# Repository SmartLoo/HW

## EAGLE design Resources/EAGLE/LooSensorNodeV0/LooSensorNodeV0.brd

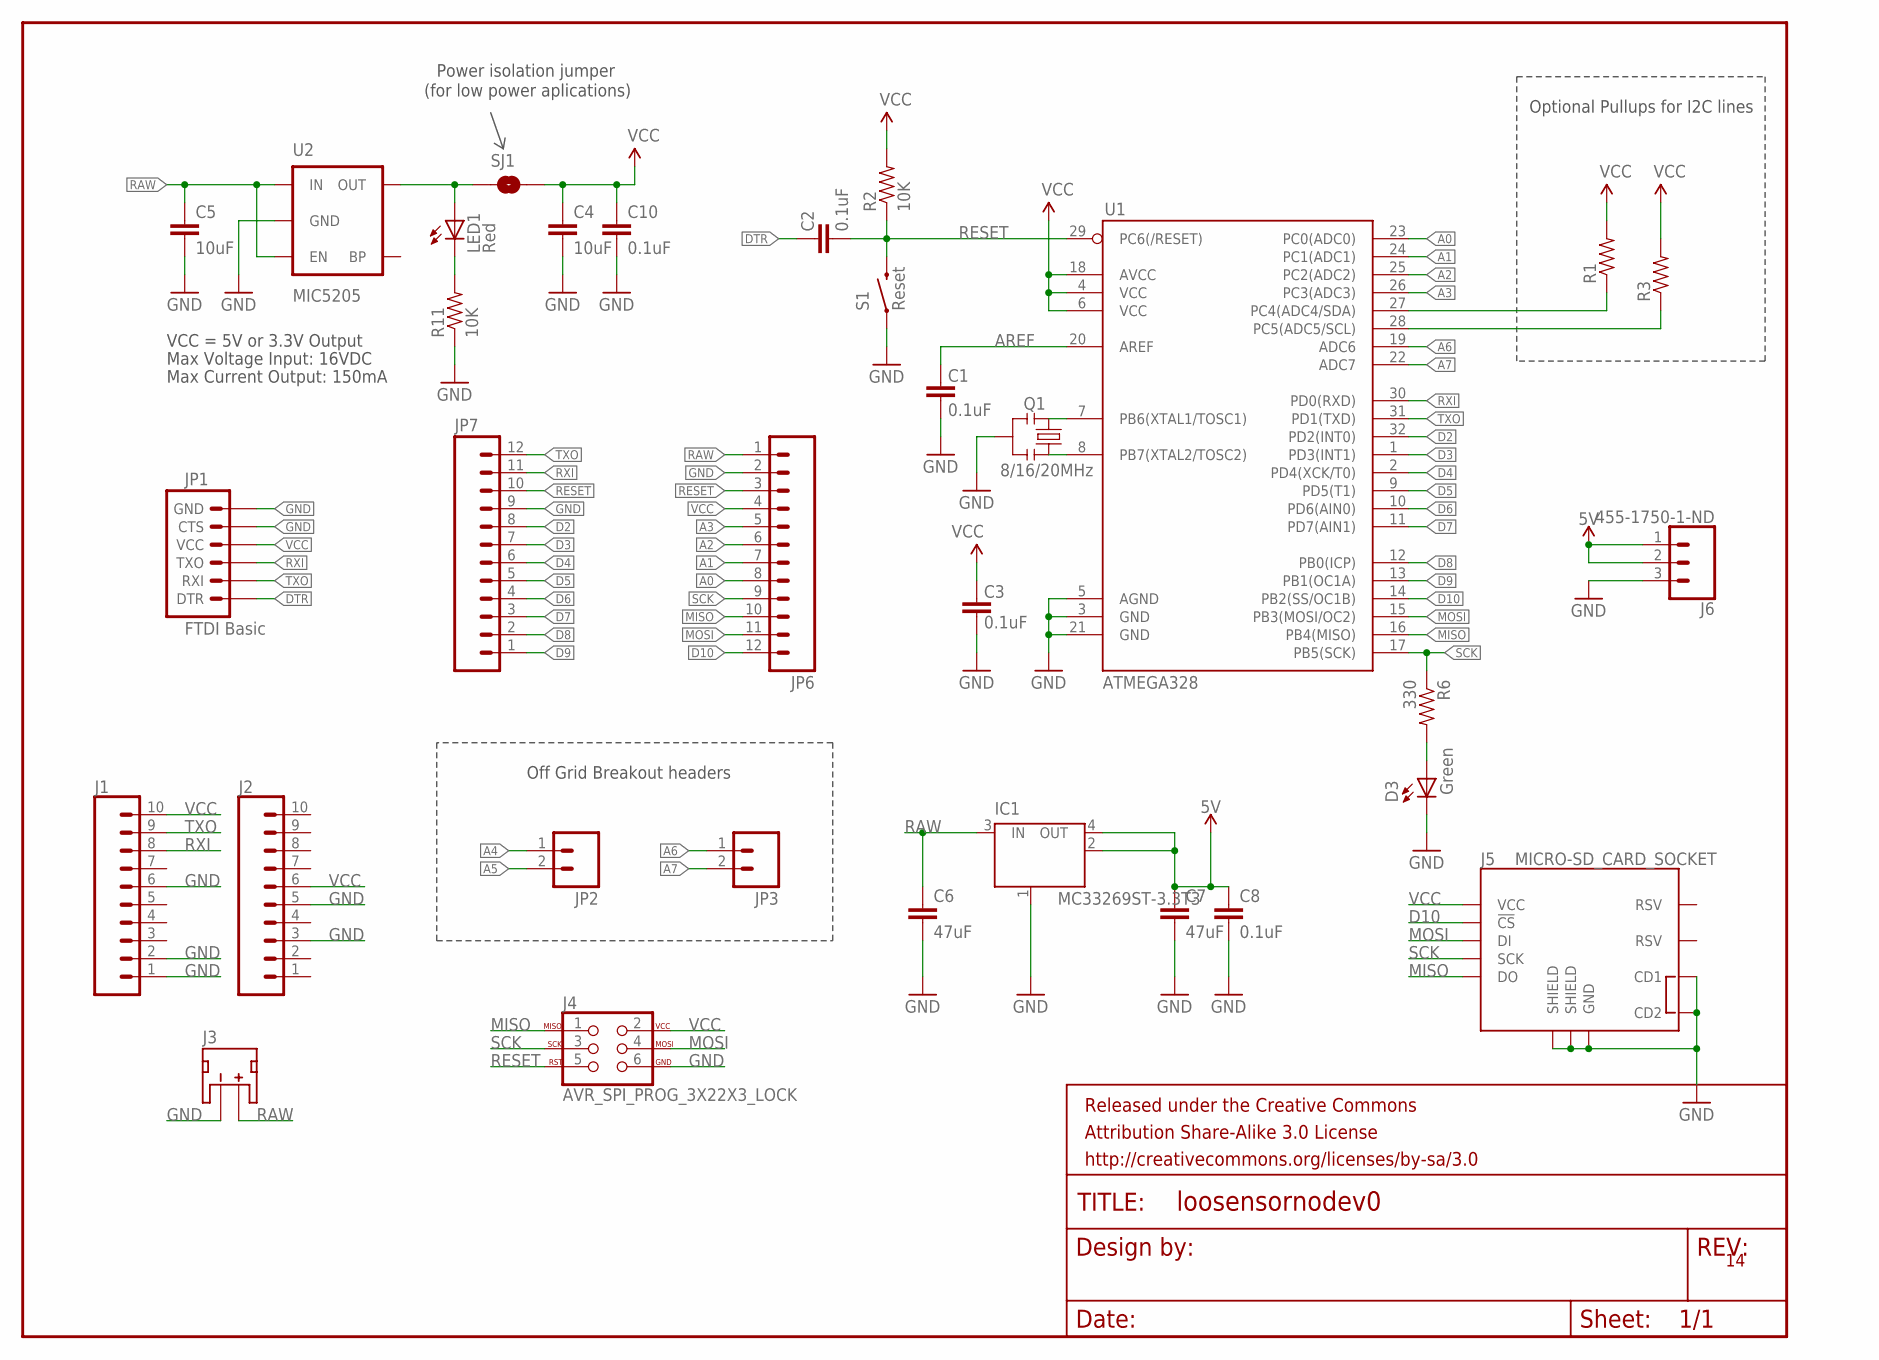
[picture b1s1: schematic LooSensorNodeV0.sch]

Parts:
C1, C2, C3, C10: 0.1uF; 0603-CAP
C4, C5: 10uF; 0603
C6, C7: 47uF; 1210
C8: 0.1uF; 0603
D3: Green; 0603-LED-ALT1
FRAME1: FRAME-LETTER; CREATIVE_COMMONS
IC1: MC33269ST-3.3T3; SOT223
J1, J2: CONN_102MM; 1X10-2MM
J3: JST_2MM_MALE; JST-2-SMD
J4: AVR_SPI_PROG_3X22X3_LOCK; 2X3_LOCK
J5: MICRO-SD_CARD_SOCKET; MICRO-SD-SOCKET
J6: 455-1750-1-ND; 1X03
JP1: FTDI Basic; 1X06
JP2, JP3: M02PTH; 1X02
JP6, JP7: M12PTH; 1X12
LED1: Red; 0603-LED-ALT1
Q1: 8/16/20MHz; RESONATOR-SMD-1:1
R1, R3: RESISTOR0603-RES; 0603-RES
R2, R11: 10K; 0603-RES
R6: 330; 0603-RES
S1: Reset; TACTILE-SWITCH-SMD-ALT01
SJ1: SOLDERJUMPERNC; SJ_2S
U1: ATMEGA328; TQFP32-08
U2: MIC5205; SOT23-5

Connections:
5V: C7.1, C8.1, IC1.2 (OUT), IC1.4 (OUT), J6.1, J6.2
A0: JP6.8, U1.23 (PC0(ADC0))
A1: JP6.7, U1.24 (PC1(ADC1))
A2: JP6.6, U1.25 (PC2(ADC2))
A3: JP6.5, U1.26 (PC3(ADC3))
A4: JP2.1, R1.1, U1.27 (PC4(ADC4/SDA))
A5: JP2.2, R3.1, U1.28 (PC5(ADC5/SCL))
A6: JP3.1, U1.19 (ADC6)
A7: JP3.2, U1.22 (ADC7)
AREF: C1.2, U1.20 (AREF)
D2: JP7.8, U1.32 (PD2(INT0))
D3: JP7.7, U1.1 (PD3(INT1))
D4: JP7.6, U1.2 (PD4(XCK/T0))
D5: JP7.5, U1.9 (PD5(T1))
D6: JP7.4, U1.10 (PD6(AIN0))
D7: JP7.3, U1.11 (PD7(AIN1))
D8: JP7.2, U1.12 (PB0(ICP))
D9: JP7.1, U1.13 (PB1(OC1A))
D10: J5.CS (!CS), JP6.12, U1.14 (PB2(SS/OC1B))
DTR: C2.2, JP1.1 (DTR)
GND: C1.1, C3.1, C4.2, C5.2, C6.2, C7.2, C8.2, C10.2, D3.C, IC1.1 (GND/ADJ), J1.1, J1.2, J1.6, J2.3, J2.5, J3.1 (-), J4.6, J5.CD1, J5.CD2, J5.GND, J5.GND1 (SHIELD), J5.GND3 (SHIELD), J6.3, JP1.5 (CTS), JP1.6 (GND), JP6.2, JP7.9, Q1.2, R11.1, S1.1, S1.2 (1), U1.3 (GND), U1.5 (AGND), U1.21 (GND), U2.2 (GND)
MISO: J4.1, J5.DO, JP6.10, U1.16 (PB4(MISO))
MOSI: J4.4, J5.DI, JP6.11, U1.15 (PB3(MOSI/OC2))
unnamed: Q1.3, U1.8 (PB7(XTAL2/TOSC2))
unnamed: Q1.1, U1.7 (PB6(XTAL1/TOSC1))
unnamed: LED1.A, SJ1.1, U2.5 (OUT)
unnamed: LED1.C, R11.2
unnamed: D3.A, R6.2
RAW: C5.1, C6.1, IC1.3 (IN), J3.2 (+), JP6.1, U2.1 (IN), U2.3 (EN)
RESET: C2.1, J4.5, JP6.3, JP7.10, R2.1, S1.3 (2), S1.4 (2), U1.29 (PC6(/RESET))
RXI: J1.8, JP1.3 (TXO), JP7.11, U1.30 (PD0(RXD))
SCK: J4.3, J5.SCLK (SCK), JP6.9, R6.1, U1.17 (PB5(SCK))
TXO: J1.9, JP1.2 (RXI), JP7.12, U1.31 (PD1(TXD))
VCC: C3.2, C4.1, C10.1, J1.10, J2.6, J4.2, J5.VCC, JP1.4 (VCC), JP6.4, R1.2, R2.2, R3.2, SJ1.2, U1.4 (VCC), U1.6 (VCC), U1.18 (AVCC)

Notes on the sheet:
Max Voltage Input: 16VDC
Max Current Output: 150mA
VCC = 5V or 3.3V Output
Optional Pullups for I2C lines
Off Grid Breakout headers
Power isolation jumper
(for low power aplications)

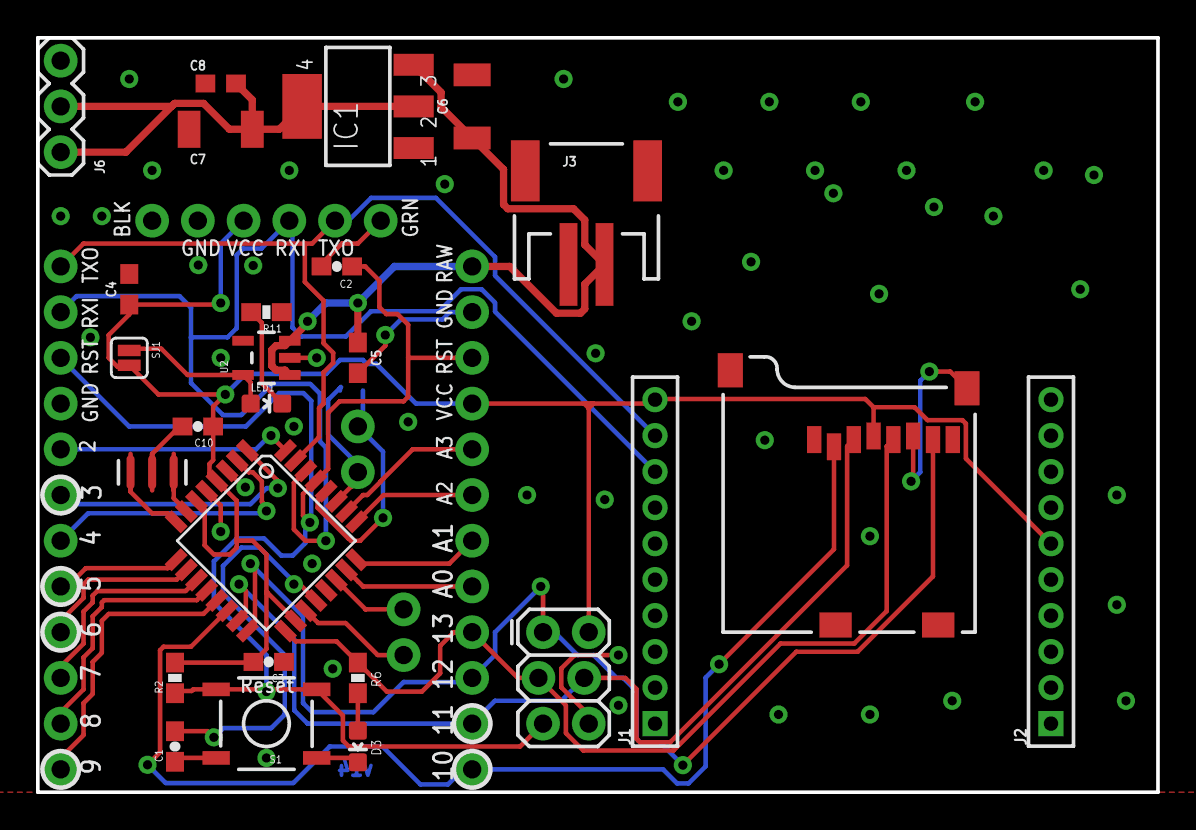
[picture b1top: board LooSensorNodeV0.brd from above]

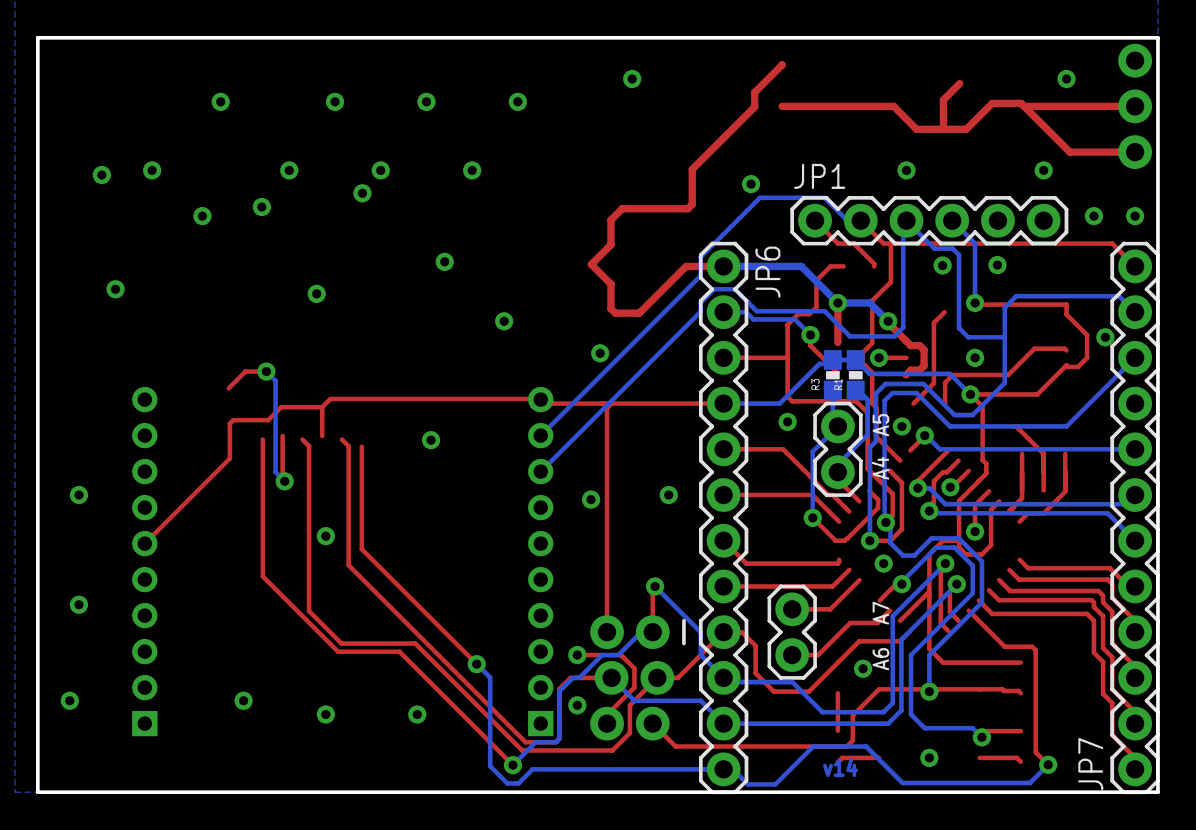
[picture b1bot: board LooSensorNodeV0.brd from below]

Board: 2 copper layers, 62.2 x 41.9 mm, 34 parts (7 on the bottom side), 34 nets.

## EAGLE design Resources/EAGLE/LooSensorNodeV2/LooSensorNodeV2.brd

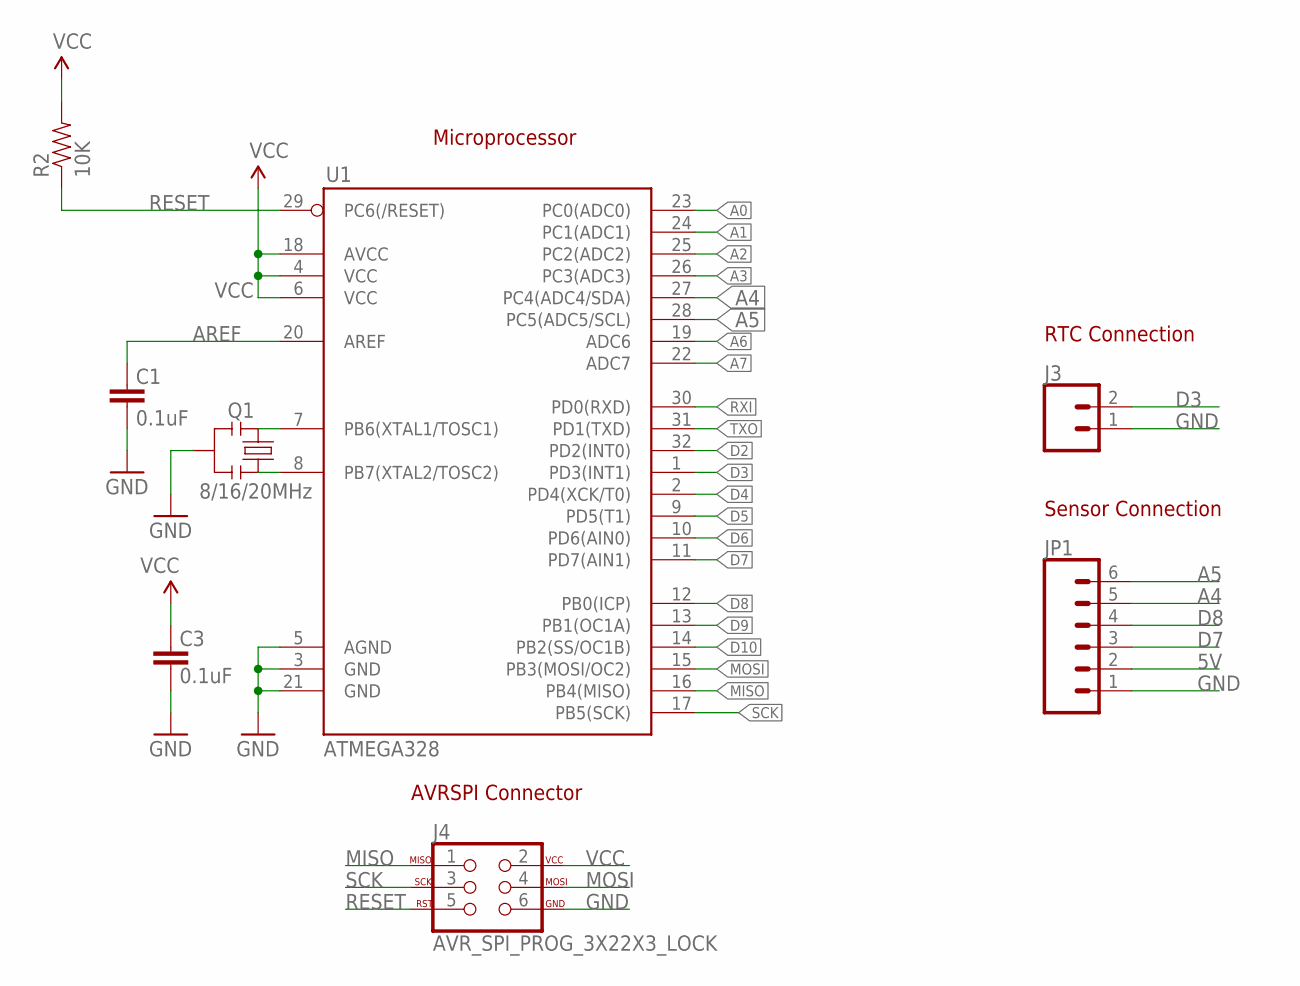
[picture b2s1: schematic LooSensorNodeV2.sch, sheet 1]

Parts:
C1, C3: 0.1uF; 0603-CAP
J3: CONN_02; 1X02
J4: AVR_SPI_PROG_3X22X3_LOCK; 2X3_LOCK
JP1: CONN_06SILK_FEMALE_PTH; 1X06
Q1: 8/16/20MHz; RESONATOR-SMD-1:1
R2: 10K; 0603-RES
U1: ATMEGA328; TQFP32-08

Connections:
5V: JP1.2; also elsewhere on the board
A0: U1.23 (PC0(ADC0))
A1: U1.24 (PC1(ADC1))
A2: U1.25 (PC2(ADC2))
A3: U1.26 (PC3(ADC3))
A4: JP1.5, U1.27 (PC4(ADC4/SDA))
A5: JP1.6, U1.28 (PC5(ADC5/SCL))
A6: U1.19 (ADC6)
A7: U1.22 (ADC7)
AREF: C1.2, U1.20 (AREF)
D2: U1.32 (PD2(INT0))
D3: J3.2, U1.1 (PD3(INT1))
D4: U1.2 (PD4(XCK/T0)); also elsewhere on the board
D5: U1.9 (PD5(T1))
D6: U1.10 (PD6(AIN0)); also elsewhere on the board
D7: JP1.3, U1.11 (PD7(AIN1))
D8: JP1.4, U1.12 (PB0(ICP))
D9: U1.13 (PB1(OC1A))
D10: U1.14 (PB2(SS/OC1B))
GND: C1.1, C3.1, J3.1, J4.6, JP1.1, Q1.2, U1.3 (GND), U1.5 (AGND), U1.21 (GND); also elsewhere on the board
MISO: J4.1, U1.16 (PB4(MISO))
MOSI: J4.4, U1.15 (PB3(MOSI/OC2))
unnamed: Q1.3, U1.8 (PB7(XTAL2/TOSC2))
unnamed: Q1.1, U1.7 (PB6(XTAL1/TOSC1))
RESET: J4.5, R2.1, U1.29 (PC6(/RESET))
RXI: U1.30 (PD0(RXD)); also elsewhere on the board
SCK: J4.3, U1.17 (PB5(SCK))
TXO: U1.31 (PD1(TXD)); also elsewhere on the board
VCC: C3.2, J4.2, R2.2, U1.4 (VCC), U1.6 (VCC), U1.18 (AVCC); also elsewhere on the board

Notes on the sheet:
AVRSPI Connector
Microprocessor
Sensor Connection
RTC Connection

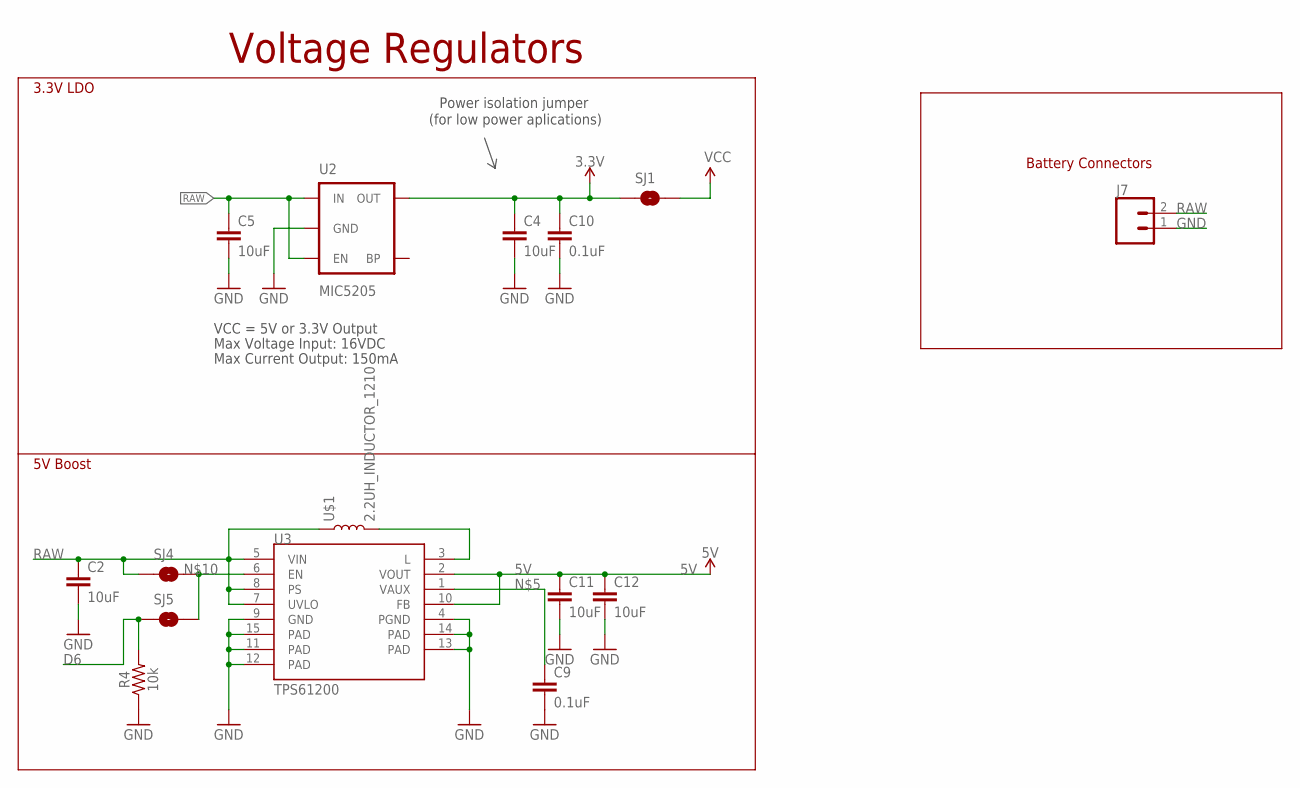
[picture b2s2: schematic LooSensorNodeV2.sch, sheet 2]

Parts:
C2, C4, C5, C11, C12: 10uF; 0603
C9: 0.1uF; 0603
C10: 0.1uF; 0603-CAP
J7: CONN_02; 1X02
R4: 10k; 0603
SJ1, SJ4, SJ5: SOLDERJUMPERNC; SJ_2S
U2: MIC5205; SOT23-5
U3: TPS61200; QFN-10_PAD
U$1: 2.2UH_INDUCTOR_1210; 1210

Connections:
3.3V: C4.1, C10.1, SJ1.1, U2.5 (OUT); also elsewhere on the board
5V: C11.1, C12.1, U3.2 (VOUT), U3.10 (FB); also elsewhere on the board
D6: R4.2, SJ5.1; also elsewhere on the board
GND: C2.2, C4.2, C5.2, C9.2, C10.2, C11.2, C12.2, J7.1, R4.1, U2.2 (GND), U3.4 (PGND), U3.9 (GND), U3.11 (PAD), U3.12 (PAD), U3.13 (PAD), U3.14 (PAD), U3.15 (PAD); also elsewhere on the board
unnamed: C9.1, U3.1 (VAUX)
unnamed: U3.3 (L), U$1.2
unnamed: SJ4.2, SJ5.2, U3.6 (EN)
RAW: C2.1, C5.1, J7.2, SJ4.1, U2.1 (IN), U2.3 (EN), U3.5 (VIN), U3.7 (UVLO), U3.8 (PS), U$1.1
VCC: SJ1.2; also elsewhere on the board

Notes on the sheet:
Max Voltage Input: 16VDC
Max Current Output: 150mA
VCC = 5V or 3.3V Output
Power isolation jumper
(for low power aplications)
3.3V LDO
5V Boost
Voltage Regulators
Battery Connectors

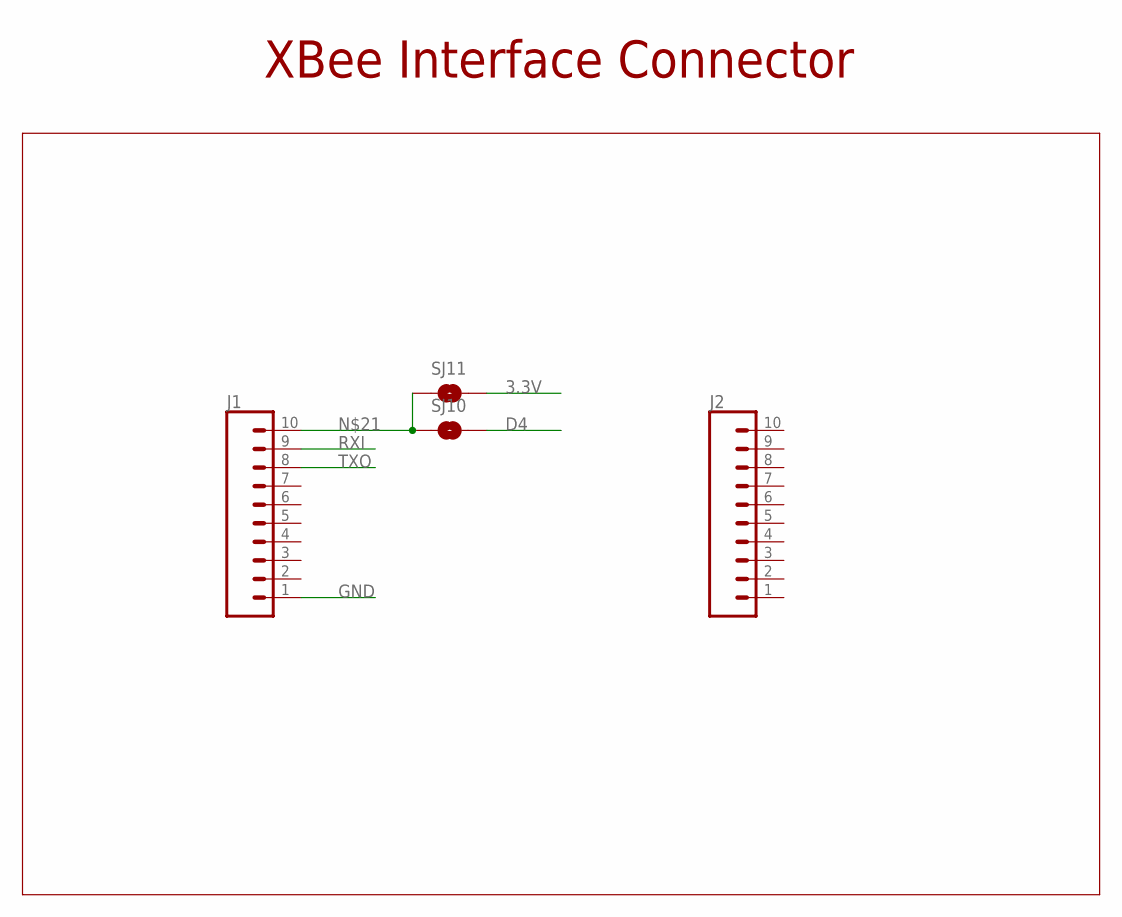
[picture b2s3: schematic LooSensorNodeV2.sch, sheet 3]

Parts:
J1, J2: CONN_102MM; 1X10-2MM
SJ10, SJ11: SOLDERJUMPERNC; SJ_2S

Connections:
3.3V: SJ11.2; also elsewhere on the board
D4: SJ10.2; also elsewhere on the board
GND: J1.1; also elsewhere on the board
unnamed: J1.10, SJ10.1, SJ11.1
RXI: J1.9; also elsewhere on the board
TXO: J1.8; also elsewhere on the board

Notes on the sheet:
XBee Interface Connector

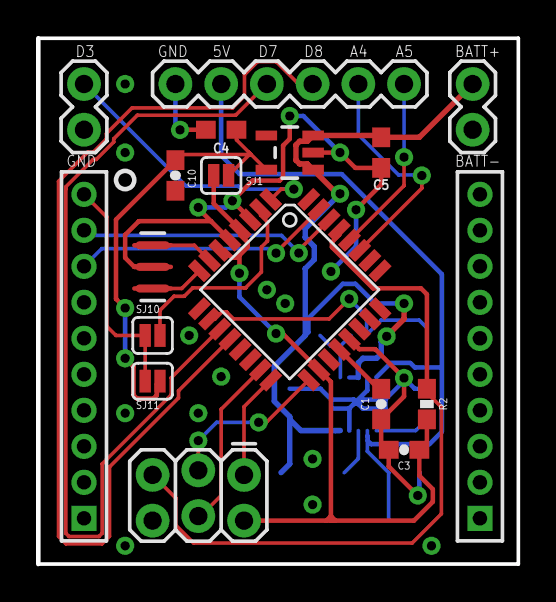
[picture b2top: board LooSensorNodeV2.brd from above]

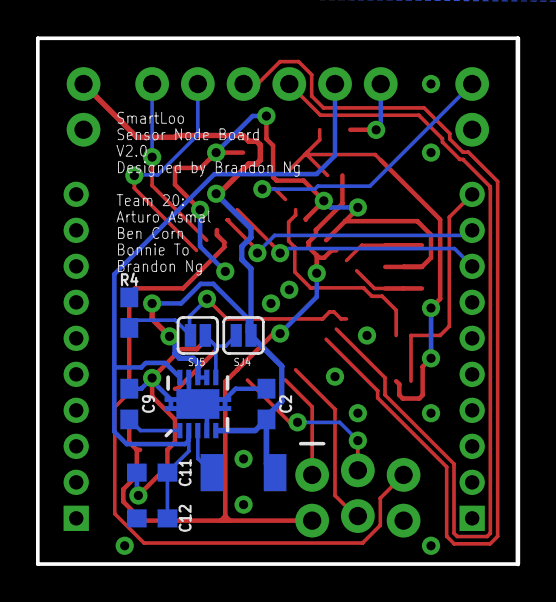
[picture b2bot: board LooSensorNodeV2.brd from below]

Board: 2 copper layers, 26.6 x 29.2 mm, 27 parts (9 on the bottom side), 25 nets.

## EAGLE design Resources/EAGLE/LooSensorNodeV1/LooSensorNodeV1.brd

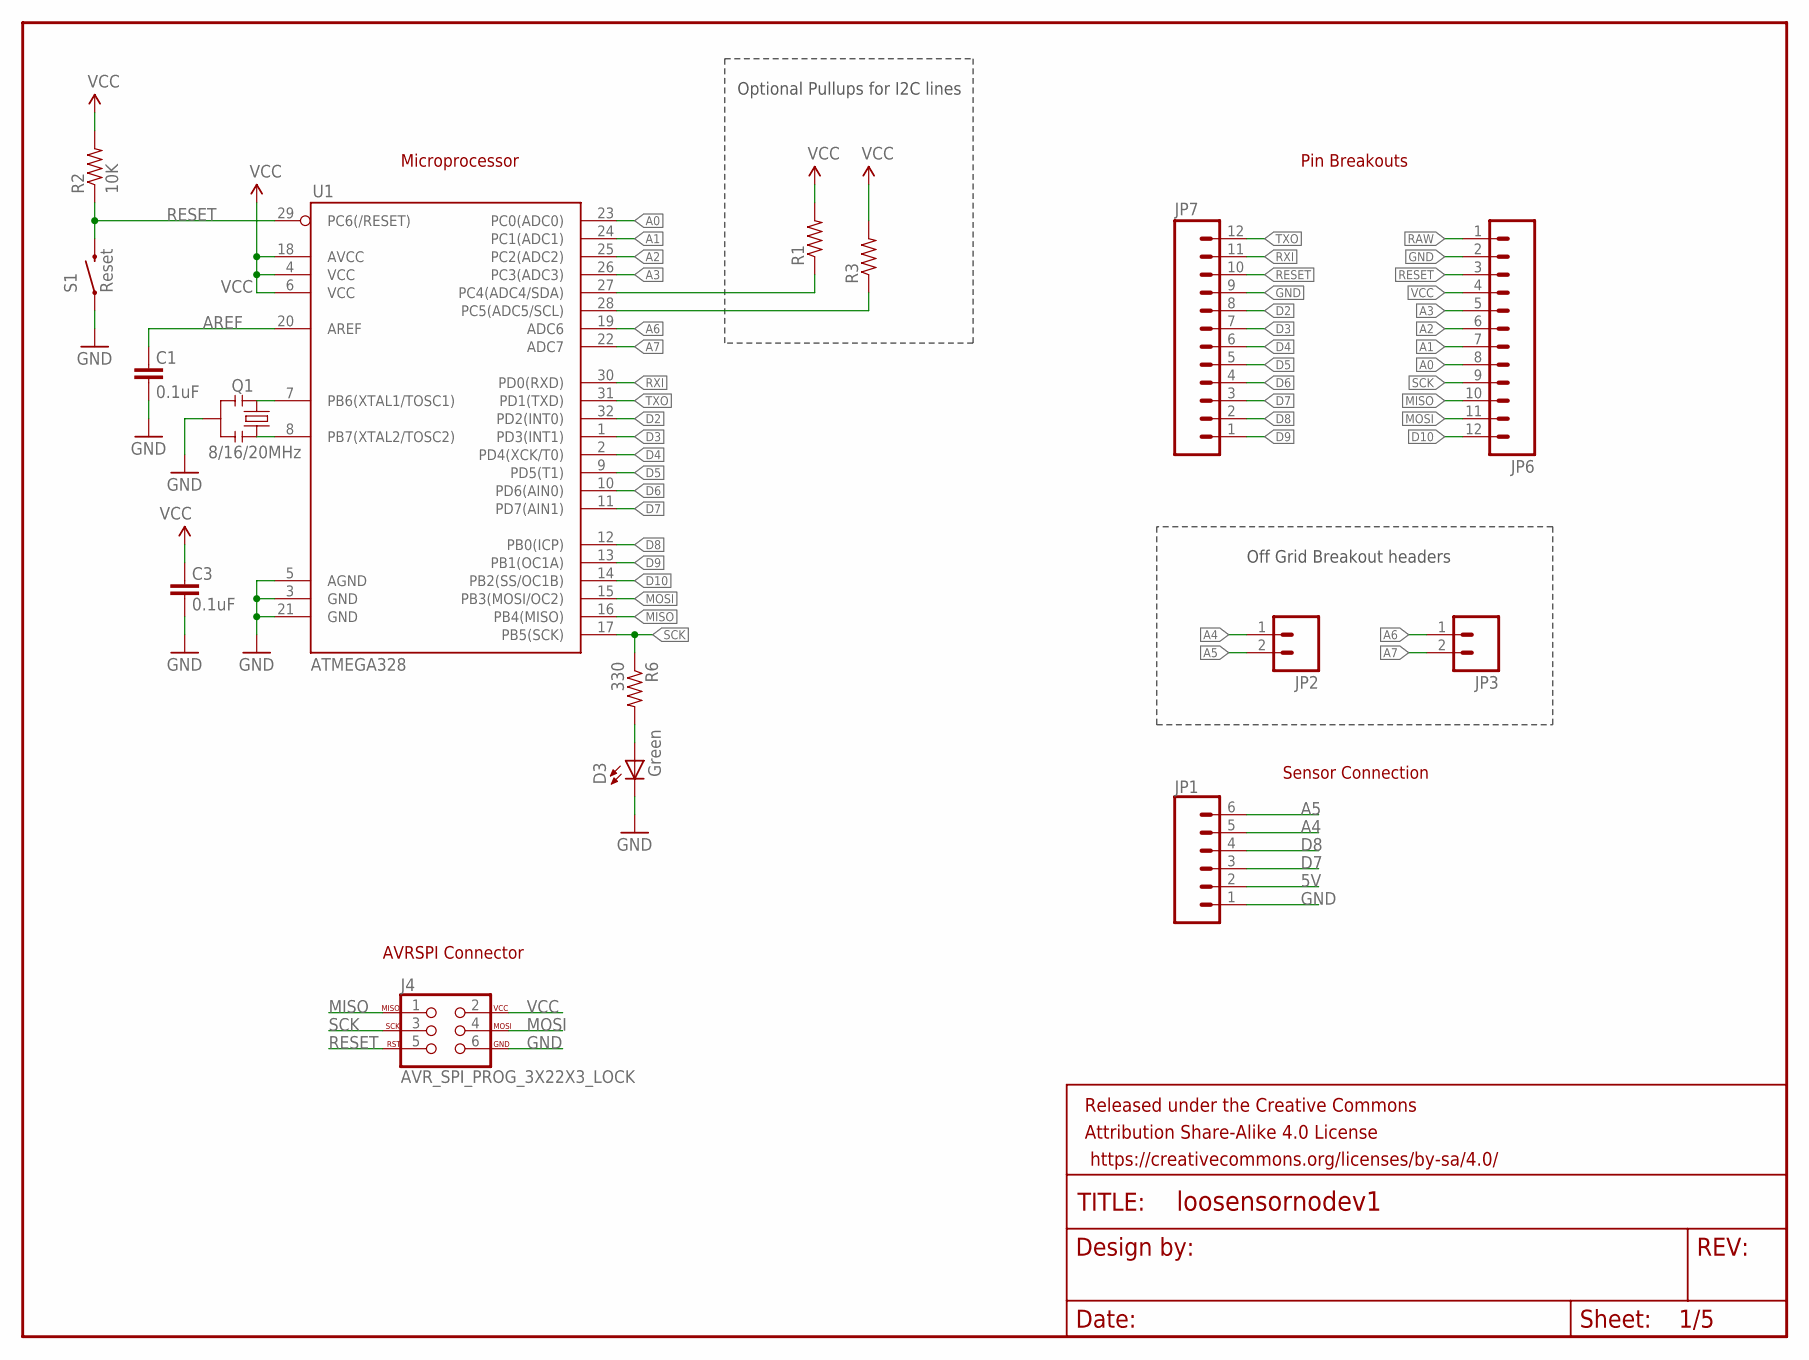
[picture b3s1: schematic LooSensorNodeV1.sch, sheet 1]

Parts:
C1, C3: 0.1uF; 0603-CAP
D3: Green; 0603-LED-ALT1
FRAME1: FRAME-LETTER; CREATIVE_COMMONS
J4: AVR_SPI_PROG_3X22X3_LOCK; 2X3_LOCK
JP1: CONN_06SILK_FEMALE_PTH; 1X06
JP2, JP3: M02PTH; 1X02
JP6, JP7: M12PTH; 1X12
Q1: 8/16/20MHz; RESONATOR-SMD-1:1
R1, R3: RESISTOR0603-RES; 0603-RES
R2: 10K; 0603-RES
R6: 330; 0603-RES
S1: Reset; TACTILE-SWITCH-SMD-ALT01
U1: ATMEGA328; TQFP32-08

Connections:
5V: JP1.2; also elsewhere on the board
A0: JP6.8, U1.23 (PC0(ADC0))
A1: JP6.7, U1.24 (PC1(ADC1))
A2: JP6.6, U1.25 (PC2(ADC2))
A3: JP6.5, U1.26 (PC3(ADC3))
A4: JP1.5, JP2.1, R1.1, U1.27 (PC4(ADC4/SDA)); also elsewhere on the board
A5: JP1.6, JP2.2, R3.1, U1.28 (PC5(ADC5/SCL)); also elsewhere on the board
A6: JP3.1, U1.19 (ADC6)
A7: JP3.2, U1.22 (ADC7)
AREF: C1.2, U1.20 (AREF)
D2: JP7.8, U1.32 (PD2(INT0)); also elsewhere on the board
D3: JP7.7, U1.1 (PD3(INT1))
D4: JP7.6, U1.2 (PD4(XCK/T0)); also elsewhere on the board
D5: JP7.5, U1.9 (PD5(T1)); also elsewhere on the board
D6: JP7.4, U1.10 (PD6(AIN0)); also elsewhere on the board
D7: JP1.3, JP7.3, U1.11 (PD7(AIN1))
D8: JP1.4, JP7.2, U1.12 (PB0(ICP))
D9: JP7.1, U1.13 (PB1(OC1A))
D10: JP6.12, U1.14 (PB2(SS/OC1B)); also elsewhere on the board
GND: C1.1, C3.1, D3.C, J4.6, JP1.1, JP6.2, JP7.9, Q1.2, S1.1, S1.2 (1), U1.3 (GND), U1.5 (AGND), U1.21 (GND); also elsewhere on the board
MISO: J4.1, JP6.10, U1.16 (PB4(MISO)); also elsewhere on the board
MOSI: J4.4, JP6.11, U1.15 (PB3(MOSI/OC2)); also elsewhere on the board
unnamed: Q1.3, U1.8 (PB7(XTAL2/TOSC2))
unnamed: Q1.1, U1.7 (PB6(XTAL1/TOSC1))
unnamed: D3.A, R6.2
RAW: JP6.1; also elsewhere on the board
RESET: J4.5, JP6.3, JP7.10, R2.1, S1.3 (2), S1.4 (2), U1.29 (PC6(/RESET))
RXI: JP7.11, U1.30 (PD0(RXD)); also elsewhere on the board
SCK: J4.3, JP6.9, R6.1, U1.17 (PB5(SCK)); also elsewhere on the board
TXO: JP7.12, U1.31 (PD1(TXD)); also elsewhere on the board
VCC: C3.2, J4.2, JP6.4, R1.2, R2.2, R3.2, U1.4 (VCC), U1.6 (VCC), U1.18 (AVCC); also elsewhere on the board

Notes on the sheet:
Optional Pullups for I2C lines
Off Grid Breakout headers
AVRSPI Connector
Pin Breakouts
Microprocessor
Sensor Connection

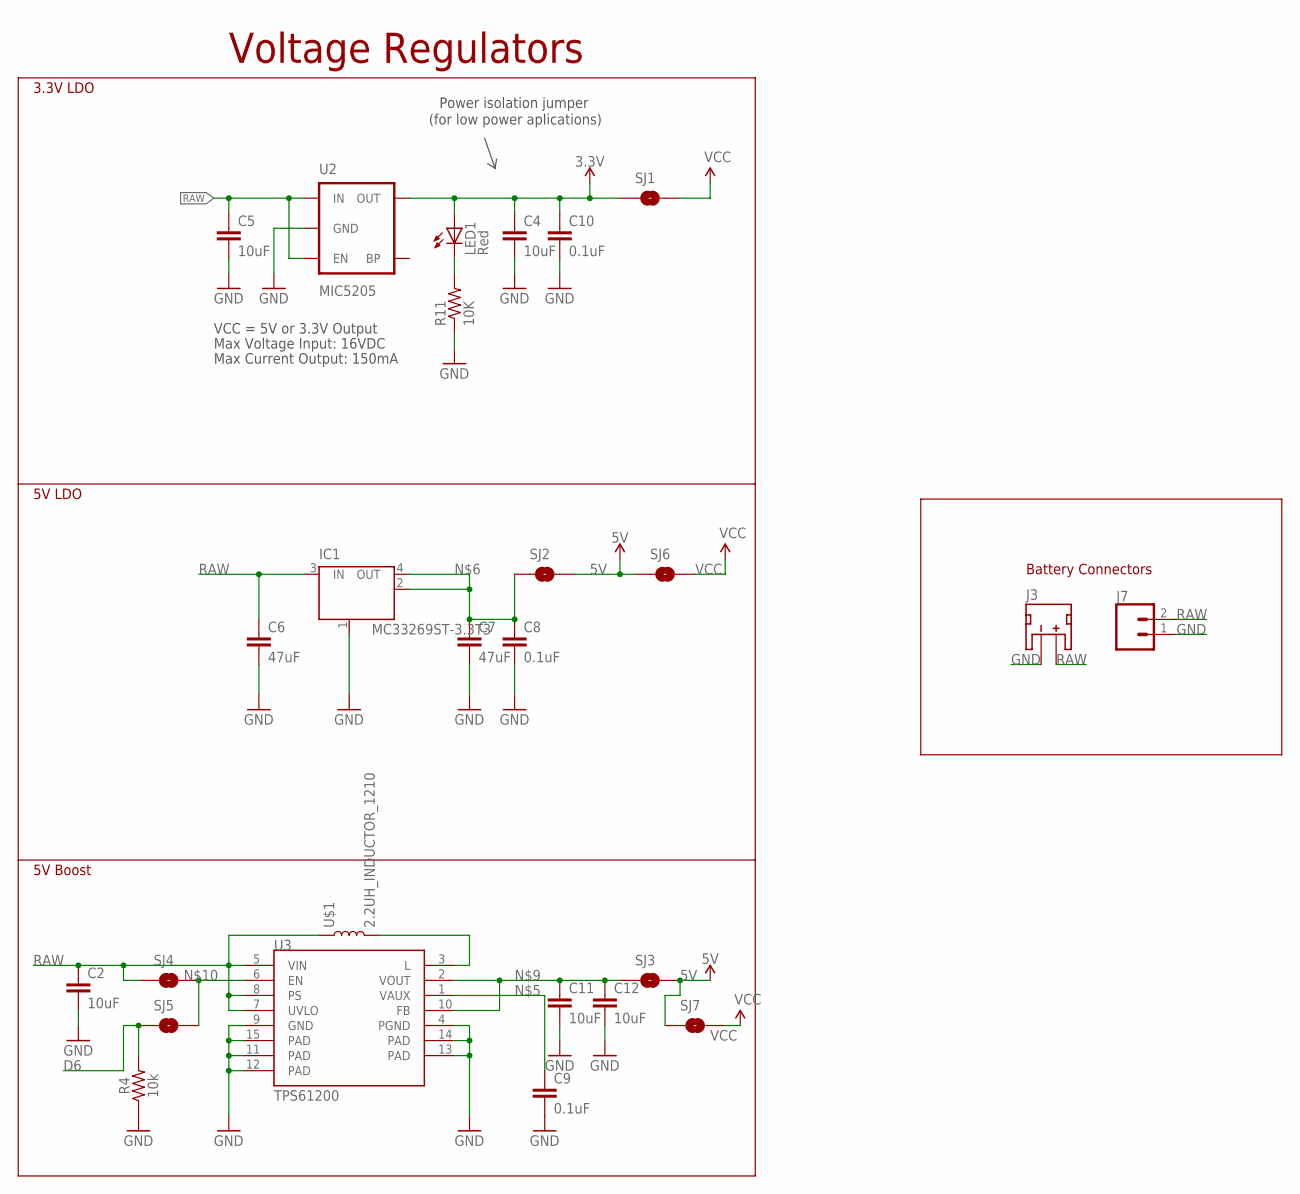
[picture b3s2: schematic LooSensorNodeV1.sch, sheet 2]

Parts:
C2, C4, C5, C11, C12: 10uF; 0603
C6, C7: 47uF; 1210
C8, C9: 0.1uF; 0603
C10: 0.1uF; 0603-CAP
IC1: MC33269ST-3.3T3; SOT223
J3: JST_2MM_MALE; JST-2-SMD
J7: CONN_02; 1X02
LED1: Red; 0603-LED-ALT1
R4: 10k; 0603
R11: 10K; 0603-RES
SJ1, SJ2, SJ3, SJ4, SJ5, SJ6, SJ7: SOLDERJUMPERNC; SJ_2S
U2: MIC5205; SOT23-5
U3: TPS61200; QFN-10_PAD
U$1: 2.2UH_INDUCTOR_1210; 1210

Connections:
3.3V: C4.1, C10.1, LED1.A, SJ1.1, U2.5 (OUT); also elsewhere on the board
5V: SJ2.2, SJ3.2, SJ6.1, SJ7.1; also elsewhere on the board
D6: R4.2, SJ5.1; also elsewhere on the board
GND: C2.2, C4.2, C5.2, C6.2, C7.2, C8.2, C9.2, C10.2, C11.2, C12.2, IC1.1 (GND/ADJ), J3.1 (-), J7.1, R4.1, R11.1, U2.2 (GND), U3.4 (PGND), U3.9 (GND), U3.11 (PAD), U3.12 (PAD), U3.13 (PAD), U3.14 (PAD), U3.15 (PAD); also elsewhere on the board
unnamed: LED1.C, R11.2
unnamed: C9.1, U3.1 (VAUX)
unnamed: C7.1, C8.1, IC1.2 (OUT), IC1.4 (OUT), SJ2.1
unnamed: U3.3 (L), U$1.2
unnamed: C11.1, C12.1, SJ3.1, U3.2 (VOUT), U3.10 (FB)
unnamed: SJ4.2, SJ5.2, U3.6 (EN)
RAW: C2.1, C5.1, C6.1, IC1.3 (IN), J3.2 (+), J7.2, SJ4.1, U2.1 (IN), U2.3 (EN), U3.5 (VIN), U3.7 (UVLO), U3.8 (PS), U$1.1; also elsewhere on the board
VCC: SJ1.2, SJ6.2, SJ7.2; also elsewhere on the board

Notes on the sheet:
Max Voltage Input: 16VDC
Max Current Output: 150mA
VCC = 5V or 3.3V Output
Power isolation jumper
(for low power aplications)
3.3V LDO
5V LDO
5V Boost
Voltage Regulators
Battery Connectors

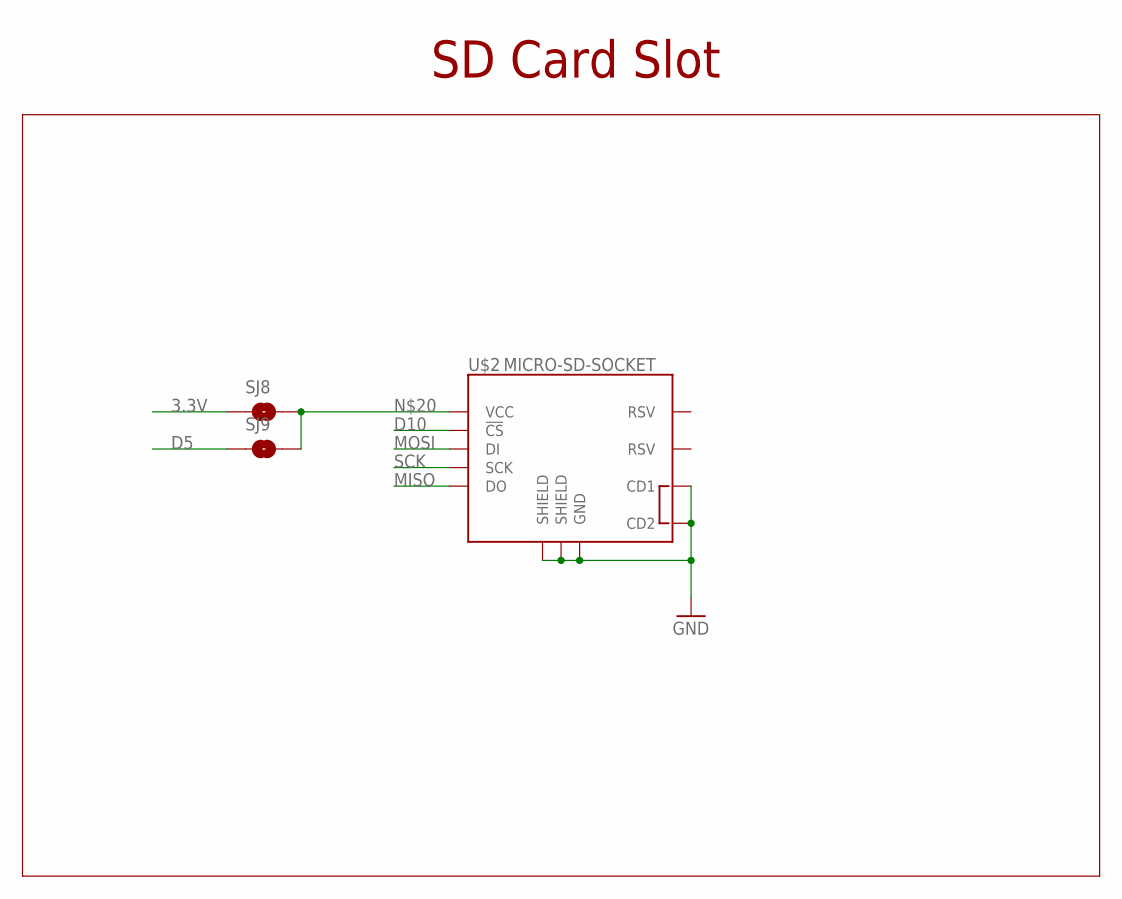
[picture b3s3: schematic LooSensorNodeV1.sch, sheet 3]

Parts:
SJ8, SJ9: SOLDERJUMPERNC; SJ_2S
U$2: MICRO-SD-SOCKET

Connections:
3.3V: SJ8.1; also elsewhere on the board
D5: SJ9.1; also elsewhere on the board
D10: U$2.CS (!CS); also elsewhere on the board
GND: U$2.CD1, U$2.CD2, U$2.GND, U$2.GND1 (SHIELD), U$2.GND3 (SHIELD); also elsewhere on the board
MISO: U$2.DO; also elsewhere on the board
MOSI: U$2.DI; also elsewhere on the board
unnamed 33: SJ8.2, SJ9.2, U$2.VCC; also elsewhere on the board
SCK: U$2.SCLK (SCK); also elsewhere on the board

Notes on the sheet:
SD Card Slot

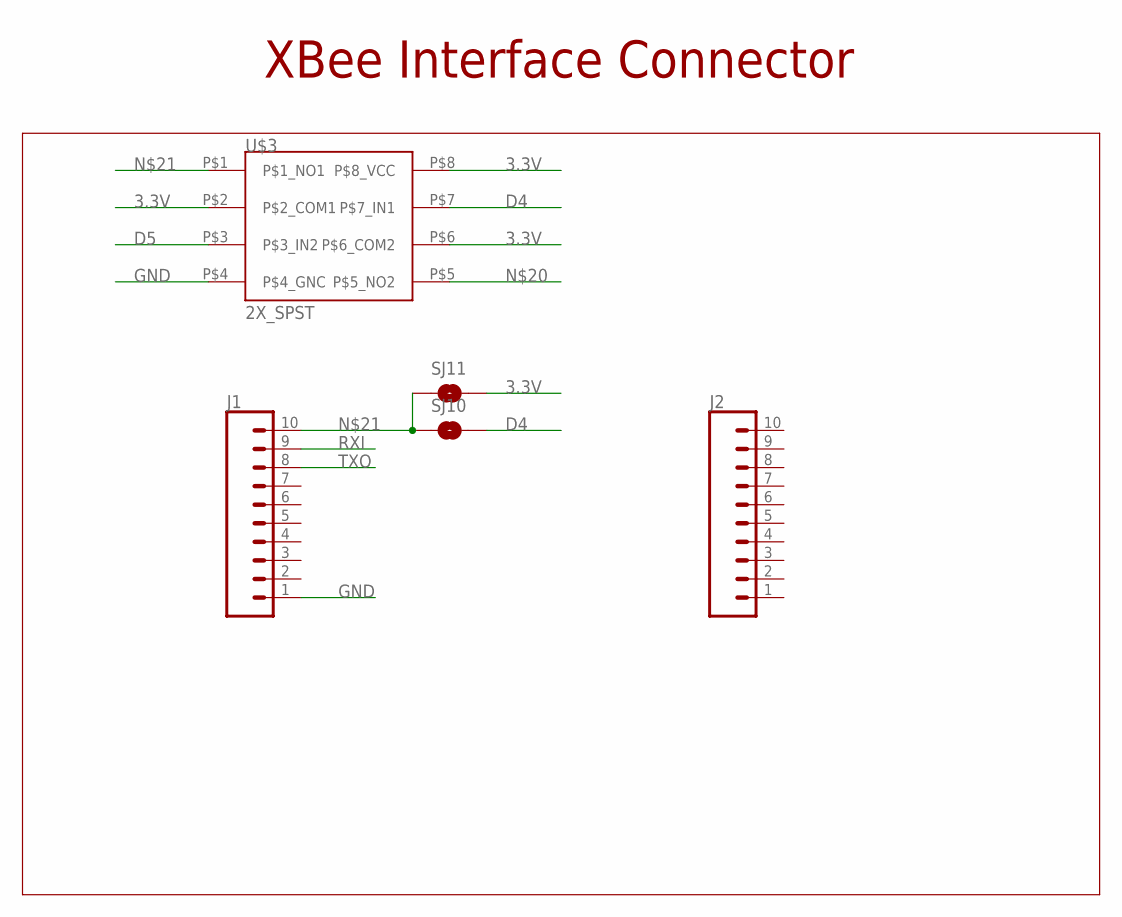
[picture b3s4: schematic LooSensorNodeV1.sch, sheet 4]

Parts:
J1, J2: CONN_102MM; 1X10-2MM
SJ10, SJ11: SOLDERJUMPERNC; SJ_2S
U$3: 2X_SPST

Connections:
3.3V: SJ11.2, U$3.P$2 (P$2_COM1), U$3.P$6 (P$6_COM2), U$3.P$8 (P$8_VCC); also elsewhere on the board
D4: SJ10.2, U$3.P$7 (P$7_IN1); also elsewhere on the board
D5: U$3.P$3 (P$3_IN2); also elsewhere on the board
GND: J1.1, U$3.P$4 (P$4_GNC); also elsewhere on the board
unnamed 33: U$3.P$5 (P$5_NO2); also elsewhere on the board
unnamed: J1.10, SJ10.1, SJ11.1, U$3.P$1 (P$1_NO1)
RXI: J1.9; also elsewhere on the board
TXO: J1.8; also elsewhere on the board

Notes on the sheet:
XBee Interface Connector

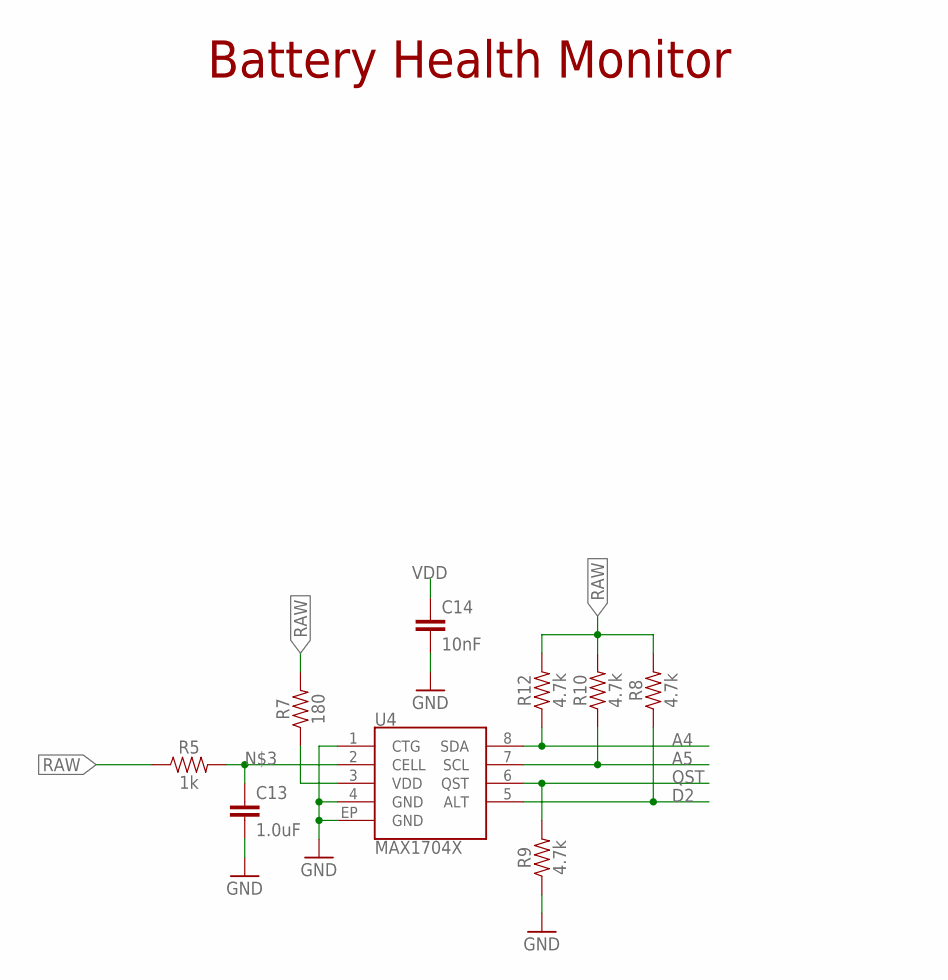
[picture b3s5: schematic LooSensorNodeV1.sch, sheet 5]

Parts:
C13: 1.0uF; 0603
C14: 10nF; 0603
R5: 1k; 0603
R7: 180; 0603
R8, R9, R10, R12: 4.7k; 0603
U4: MAX1704X; TDFN-8

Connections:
A4: R12.1, U4.8 (SDA); also elsewhere on the board
A5: R10.1, U4.7 (SCL); also elsewhere on the board
D2: R8.1, U4.5 (ALT); also elsewhere on the board
GND: C13.2, C14.2, R9.1, U4.1 (CTG), U4.4 (GND), U4.EP (GND); also elsewhere on the board
unnamed: C13.1, R5.2, U4.2 (CELL)
QST: R9.2, U4.6 (QST)
RAW: R5.1, R7.2, R8.2, R10.2, R12.2; also elsewhere on the board
VDD: C14.1, R7.1, U4.3 (VDD)

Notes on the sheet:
Battery Health Monitor

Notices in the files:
parts and their libraries:
SparkFun-Aesthetics: Licensing: CC v3.0 Share-Alike You are welcome to use this library for commercial purposes.
SparkFun-Aesthetics: Released under the Creative Commons Attribution Share-Alike 3.0 License
SparkFun-Aesthetics: http://creativecommons.org/licenses/by-sa/3.0
